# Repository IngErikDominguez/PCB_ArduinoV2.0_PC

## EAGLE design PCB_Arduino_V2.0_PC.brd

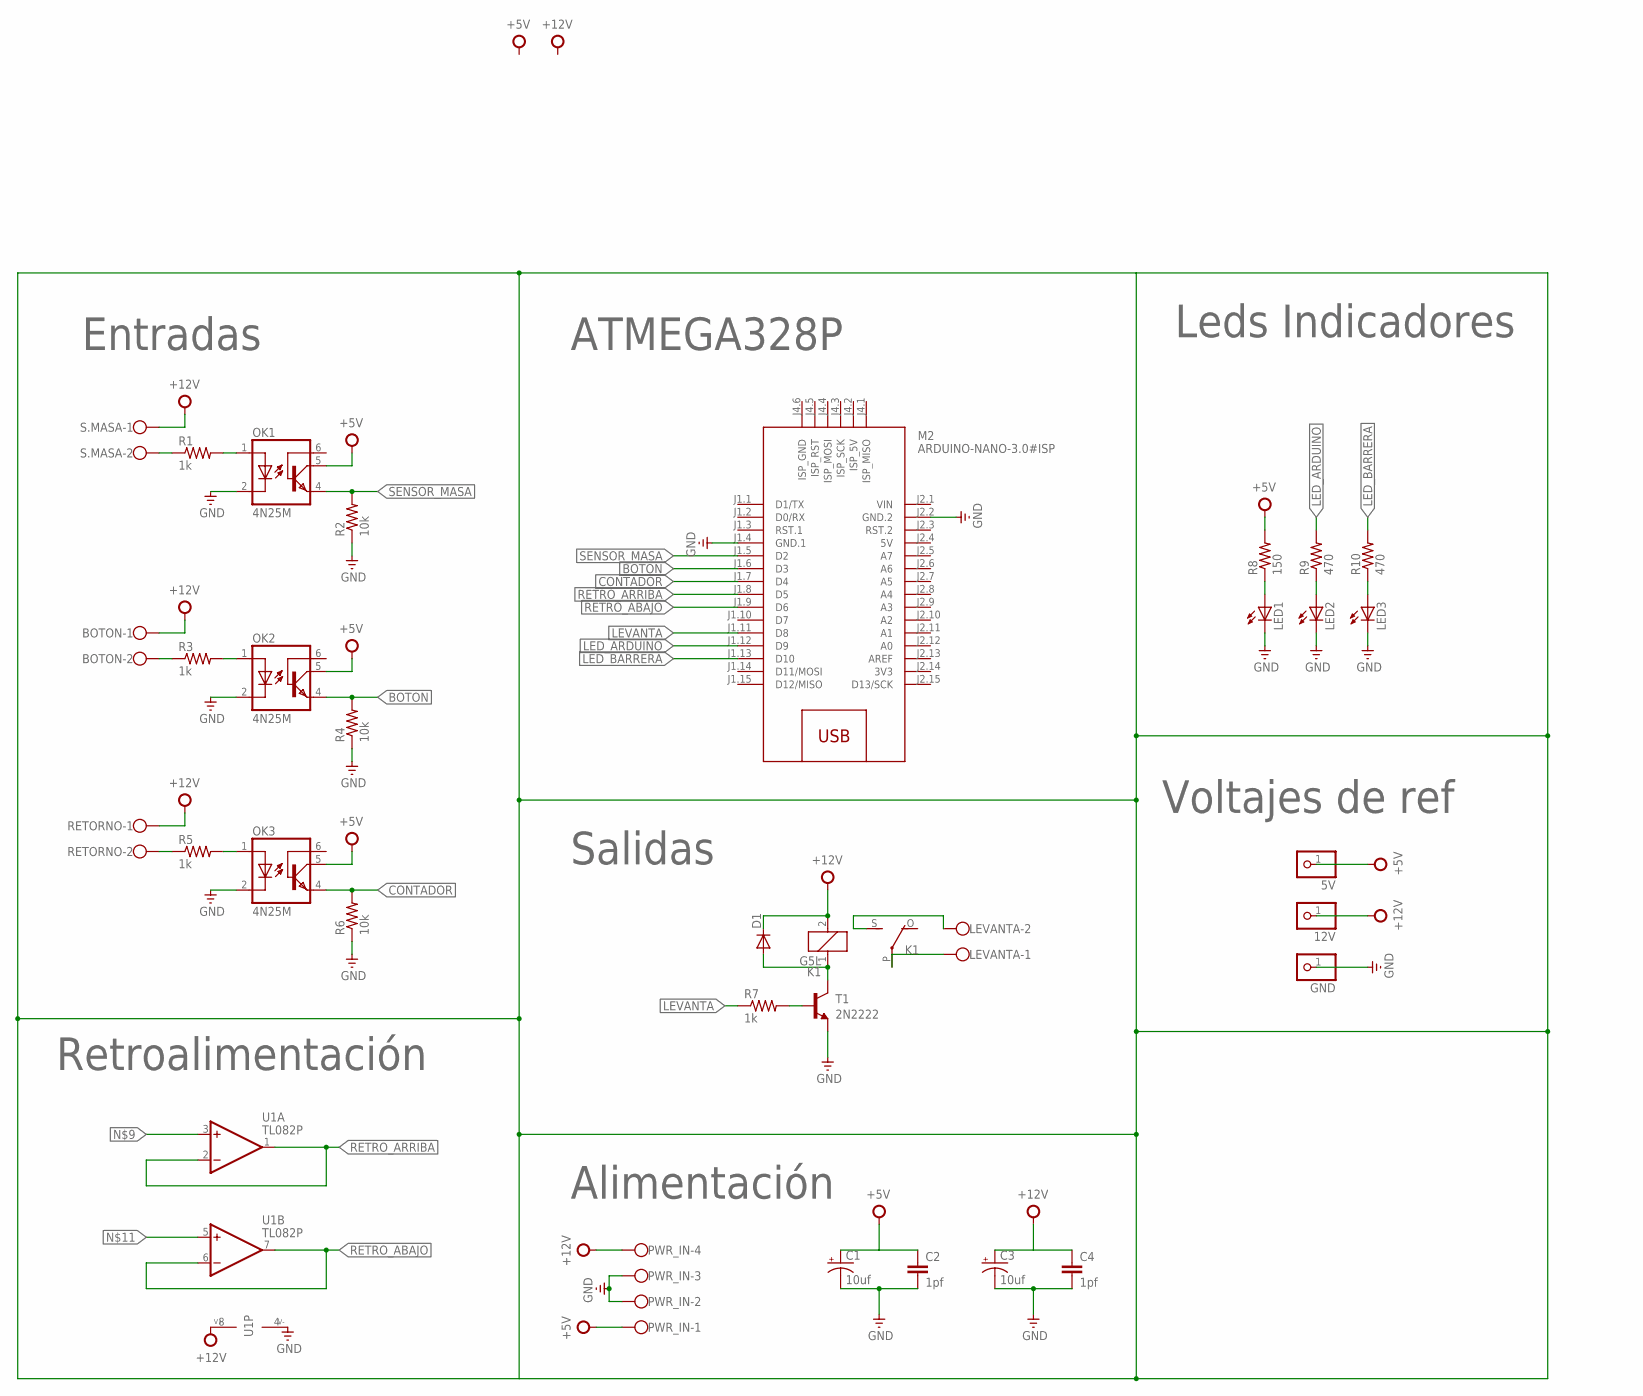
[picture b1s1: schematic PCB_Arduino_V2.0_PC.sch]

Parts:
5V, 12V: PINHD-1X1; 1X01
BOTON: W237-102
C1, C3: 10uf; E2,5-6
C2, C4: 1pf; C2.5-3
D1: 1N4148DO35-7; DO35-7
GND: PINHD-1X1; 1X01
K1: G5L; G5LE
LED1, LED2, LED3: LED5MM
LEVANTA: W237-102
M2: ARDUINO-NANO-3.0#ISP
OK1, OK2, OK3: 4N25M; DIL06
PWR_IN: W237-4
R1, R3, R5, R7: 1k; 0207/7
R2, R4, R6: 10k; 0207/7
R8: 150; 0207/7
R9, R10: 470; 0207/7
RETORNO: W237-102
S.MASA: W237-102
T1: 2N2222; TO18
U1: TL082P; DIL08

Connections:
3V3: M2.J2.14 (3V3)
5V: M2.J2.4 (5V)
+5V: 5V.1, C1.+, C2.1, OK1.5 (COL), OK2.5 (COL), OK3.5 (COL), PWR_IN.1, R8.2
+12V: 12V.1, BOTON.1, C3.+, C4.1, D1.C, K1.2, PWR_IN.4, RETORNO.1, S.MASA.1, U1.8 (V+)
BOTON: M2.J1.6 (D3), OK2.4 (EMI), R4.2
CONTADOR: M2.J1.7 (D4), OK3.4 (EMI), R6.2
GND: C1.-, C2.2, C3.-, C4.2, GND.1, LED1.K (C), LED2.K (C), LED3.K (C), M2.J1.4 (GND.1), M2.J2.2 (GND.2), OK1.2 (C), OK2.2 (C), OK3.2 (C), PWR_IN.2, PWR_IN.3, R2.1, R4.1, R6.1, T1.1 (E), U1.4 (V-)
LED_ARDUINO: M2.J1.12 (D9), R9.2
LED_BARRERA: M2.J1.13 (D10), R10.2
LEVANTA: M2.J1.11 (D8), R7.1
unnamed: R1.1, S.MASA.2
unnamed: BOTON.2, R3.1
unnamed: OK1.1 (A), R1.2
unnamed: OK2.1 (A), R3.2
unnamed: D1.A, K1.1, T1.3 (C)
unnamed: R5.1, RETORNO.2
unnamed: OK3.1 (A), R5.2
unnamed: R7.2, T1.2 (B)
unnamed: K1.S, LEVANTA.2
unnamed: K1.P, LEVANTA.1
unnamed: LED1.A, R8.1
unnamed: LED2.A, R9.1
unnamed: LED3.A, R10.1
RETRO_ABAJO: M2.J1.9 (D6), U1.6 (-IN), U1.7 (OUT)
RETRO_ARRIBA: M2.J1.8 (D5), U1.1 (OUT), U1.2 (-IN)
SENSOR_MASA: M2.J1.5 (D2), OK1.4 (EMI), R2.2
VIN: M2.J2.1 (VIN)

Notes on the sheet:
Entradas
Retroalimentación
ATMEGA328P
Salidas
Alimentación
Leds Indicadores
Voltajes de ref

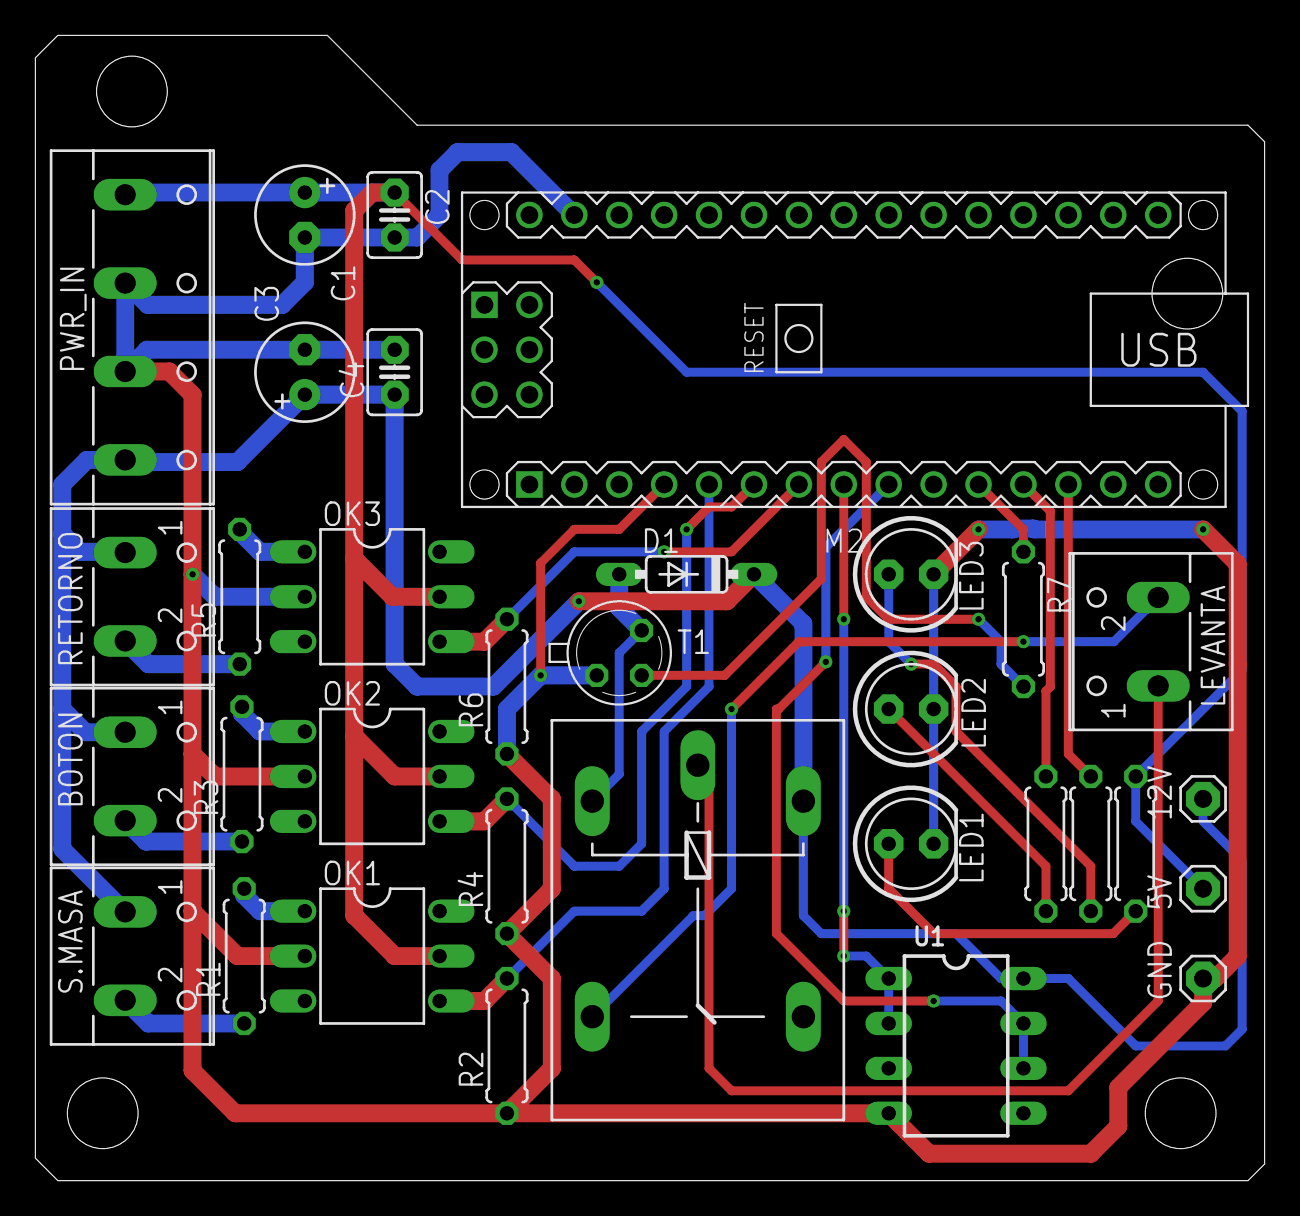
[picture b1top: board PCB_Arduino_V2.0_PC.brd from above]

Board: 2 copper layers, 69.5 x 64.8 mm, 33 parts (0 on the bottom side), 24 nets.

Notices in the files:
parts and their libraries:
diy-modules: Released under the Creative Commons Attribution 4.0 International License: http://creativecommons.org/licenses/by/4.0
op-amp: Copyright (C) 2006 by Bob Starr
